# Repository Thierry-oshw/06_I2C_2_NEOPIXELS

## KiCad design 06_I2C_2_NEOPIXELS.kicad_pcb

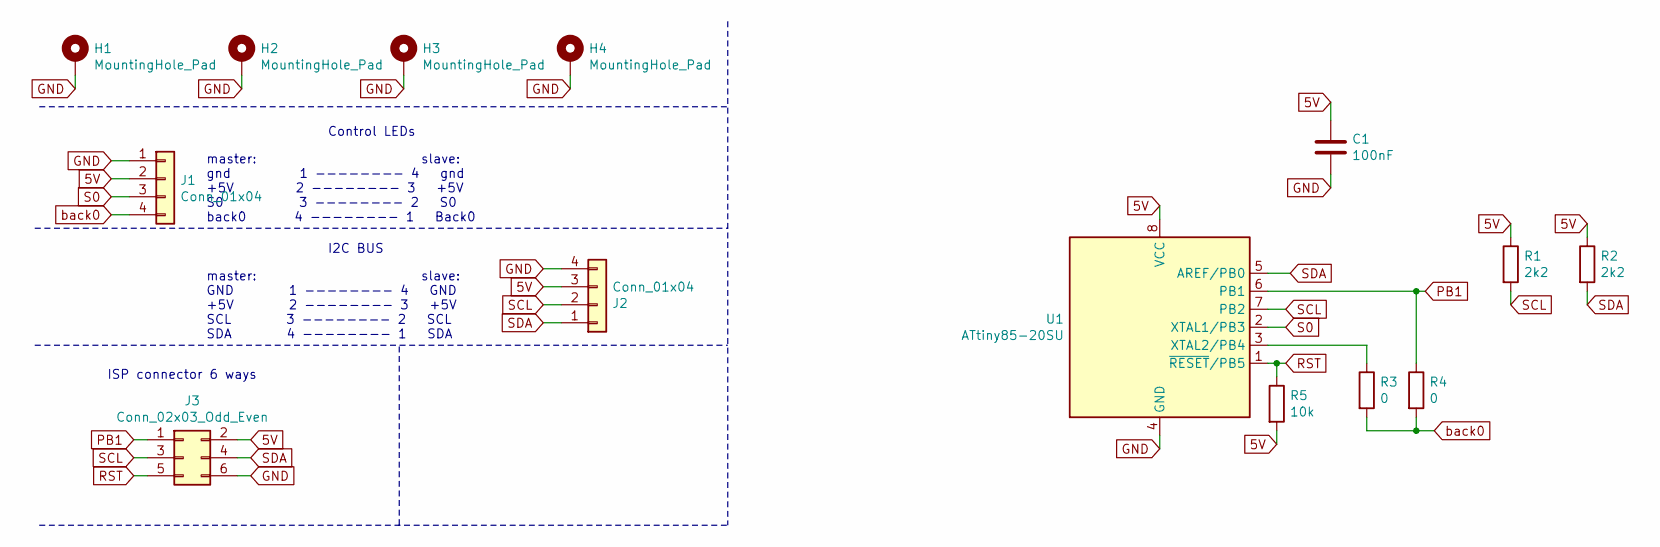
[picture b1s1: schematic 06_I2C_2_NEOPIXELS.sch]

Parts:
C1: 100nF; C_0603_1608Metric
H1, H2, H3, H4: MountingHole_Pad; MountingHole_3.2mm_M3_Pad_Via
J1, J2: Conn_01x04; JST_XH_S4B-XH-A_1x04_P2.50mm_Horizontal
J3: Conn_02x03_Odd_Even; PinHeader_2x03_P2.54mm_Vertical
R1, R2: 2k2; R_0603_1608Metric
R3, R4: 0; R_0603_1608Metric
R5: 10k; R_0603_1608Metric
U1: ATtiny85-20SU; SOIJ-8_5.3x5.3mm_P1.27mm

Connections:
5V: C1.1, J1.2, J2.3, J3.2, R1.1, R2.1, R5.2, U1.8 (VCC)
GND: C1.2, H1.1, H2.1, H3.1, H4.1, J1.1, J2.4, J3.6, U1.4 (GND)
unnamed: R3.1, U1.3 (XTAL2/PB4)
PB1: J3.1, R4.1, U1.6 (PB1)
RST: J3.5, R5.1, U1.1 (~RESET~/PB5)
S0: J1.3, U1.2 (XTAL1/PB3)
SCL: J2.2, J3.3, R1.2, U1.7 (PB2)
SDA: J2.1, J3.4, R2.2, U1.5 (AREF/PB0)
back0: J1.4, R3.2, R4.2

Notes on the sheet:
Control LEDs
master: slave: gnd 1 -------- 4 gnd +5V 2 -------- 3 +5V S0 3 -------- 2 S0 back0 4 -------- 1 Back0
I2C BUS
master: slave: GND 1 -------- 4 GND +5V 2 -------- 3 +5V SCL 3 -------- 2 SCL SDA 4 -------- 1 SDA
ISP connector 6 ways

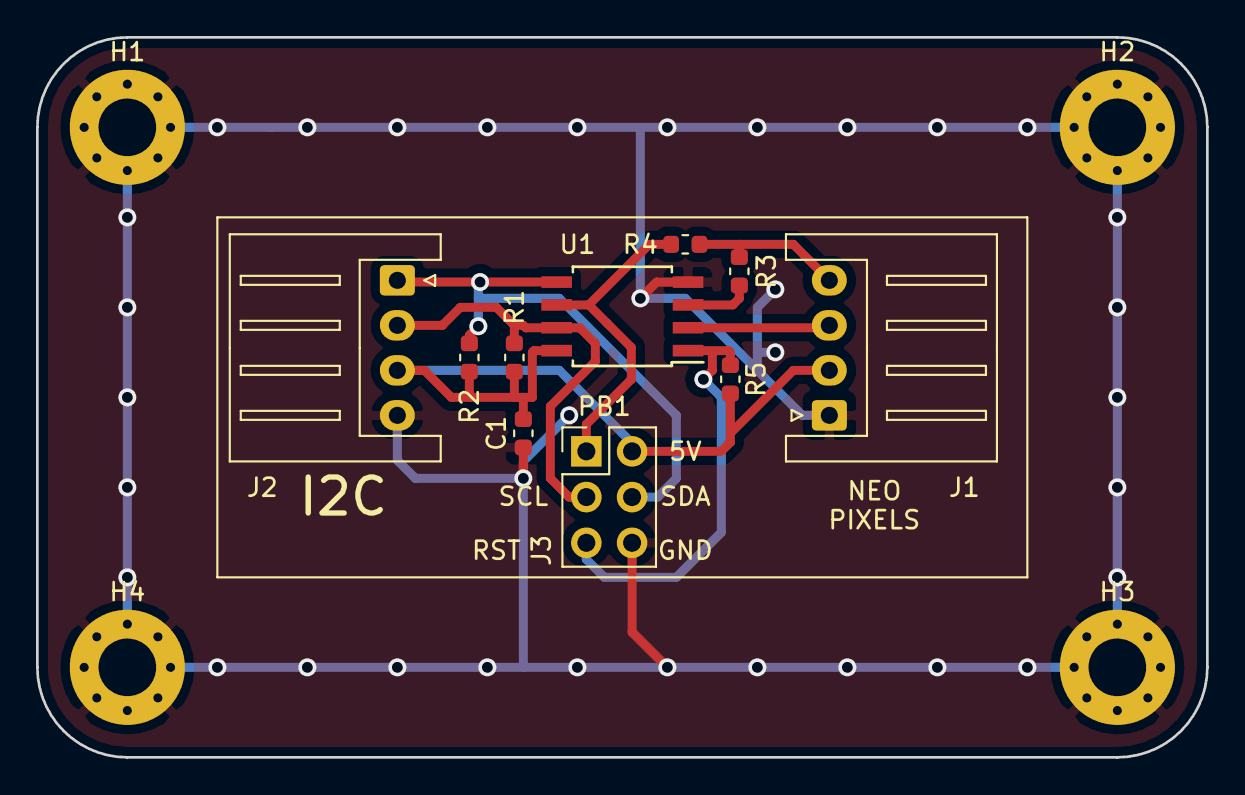
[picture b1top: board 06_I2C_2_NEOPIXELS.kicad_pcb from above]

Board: 2 copper layers, 65.0 x 40.0 mm, 14 parts (0 on the bottom side), 9 nets.

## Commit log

2020-12-09 creation
2021-01-30 added picture
2021-07-24 maj split librairies
2023-05-02 chgt nom fichier licence
